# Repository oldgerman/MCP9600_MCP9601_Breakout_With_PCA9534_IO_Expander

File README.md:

# MCP9600/MCP9601 Breakout, With PCA9534 IO Expander 

- <span style="color:rgb(255, 0, 0);">The module has a bug, don’t make a board.</span>
- <span style="color:rgb(255, 0, 0);">该模块有BUG，不要打板</span>

## PCB

## SCH

## BOM

Please see bom/ibom.html

## Connectors

1. 5.08mm Pitch 2Pin Plug

2. [OMEGA Circuit Board Thermocouple Connectors](https://www.omega.com/en-us/temperature-measurement/temperature-connectors%2C-panels-and-block-assemblies/temperature-connectors/p/PCC-OST-SMP)

## Pictures

:confused:

## Libraries

1. [PCA9534](https://github.com/alotaiba/PCA9534)
2. [MCP9600](https://github.com/sparkfun/SparkFun_MCP9600_Arduino_Library)

## Reference

1. [Microchip：MCP9600 Evaluation Board](https://www.microchip.com/adm00665-063015a)

2. [Maxim：MAX31855PMB1 Peripheral Module](https://www.maximintegrated.com/en/products/sensors/MAX31855PMB1.html)

3. [Seeed：Grove - I2C Thermocouple Amplifier MCP9600](https://wiki.seeedstudio.com/Grove-I2C_Thermocouple_Amplifier-MCP9600/)

4. [SparkFun：Qwiic Thermocouple Amplifier - MCP9600](https://www.sparkfun.com/products/16294)

5. [Adafruit：MCP9600 I2C Thermocouple Amplifier](https://www.adafruit.com/product/4101)

## Test

MCP96RL01 + T12 irons TYPE-N

| Read Thermocouple(℃) | Read Ambient(℃) | Measurements(mV) | (Ref Junction 0℃) its 90 table for N Type(mV) | (Ref Junction 0℃) its 90 table for N Type(℃) | Read Ambient + its 90 table N Type  (℃) | error(℃) | Hot air gun(W) |
| -------------------- | --------------- | ---------------- | --------------------------------------------- | -------------------------------------------- | --------------------------------------- | -------- | -------------- |
| 100                  | 24.62           | 2.1              | 2.106                                         | 78                                           | 102.62                                  | 2.62     | 314            |
| 156                  | 24.75           | 3.8              | 3.803                                         | 135                                          | 159.75                                  | 3.75     | 500            |
| 180                  | 24.56           | 4.6              | 4.618                                         | 160                                          | 184.56                                  | 4.56     | 587            |
| 190                  | 25.37           | 4.8              | 4.809                                         | 167                                          | 192.37                                  | 2.37     | 600            |

## Alert 引脚的下拉电阻

MCP9601的6个Alert引脚均为推挽输出，复位后默认状态为Alert1~4输出高电平，OC Alert和SC Alert均使能，高电平表示OC触发，SC触发，或温度警报触发，无PCF9534时，6个Alert引脚不需要下拉电阻，Alert的3.3V高电平可正常输出给MCU

若焊接了PCF9534，则PCF9534复位的寄存器默认值将io 0~7配置为高阻抗输出驱动器的输入，输入电压可以升高到VDD以上，最大为5.5V，此时需要焊接所有Alert pins的下拉电阻，确保Alert的高电平为3.3V

## Important premise of the data sheet

### 3.4 Push-Pull Alert Outputs (Alert 1, 2, 3, 4 and OC/SC Alert)

Alert引脚是用户可编程的推挽输出，可用于检测温度上升或下降。当环境温度超过用户设置的温度警报极限时，设备输出**高电平**信号。 对于MCP9601 / L01 / RL01，当在VSENSE引脚上检测到开路和短路条件时，OC Alert和SC Alert输出才有效，这两个Alerts也是**高电平有效**推挽输出

### 6.3.3.1开路检测技术

mcp9600和mcp9601都具有开路检测技术（即使mcp9600没有V<sub>SENSE</sub>和OC Alert引脚），区别在于mcp9601的OC Alert引脚可以当作硬件指示器

对于MCP9600 / L00 / RL00开路检测，可以使用STATUS寄存器（寄存器5-6）的输入范围位（位4）来检测开路条件。这将需要一些外部电阻，如图6-6所示。无源电路不会影响MCP9600 / L00 / RL00的精度（RB的推荐值设置为1M。连接热电偶时，输入共模电压为 0.5×VDD。当热电偶断开连接，VIN +输入端的电压为 0.66×VDD，VIN-输入端的电压下拉至VSS。此更改将强制设置输入范围位。

MCP9601 / L01 / RL01开路检测机制的工作原理类似（请参见图6-7），检测阈值指定为V<sub>SiOC</sub>和V<sub>SiNOR</sub>（请参见DC特性）。主控制器可以立即轮询状态位以检测开路条件。对于MCP9601 / L01 / RL01，可以将OC Alert引脚用作硬件指示器。

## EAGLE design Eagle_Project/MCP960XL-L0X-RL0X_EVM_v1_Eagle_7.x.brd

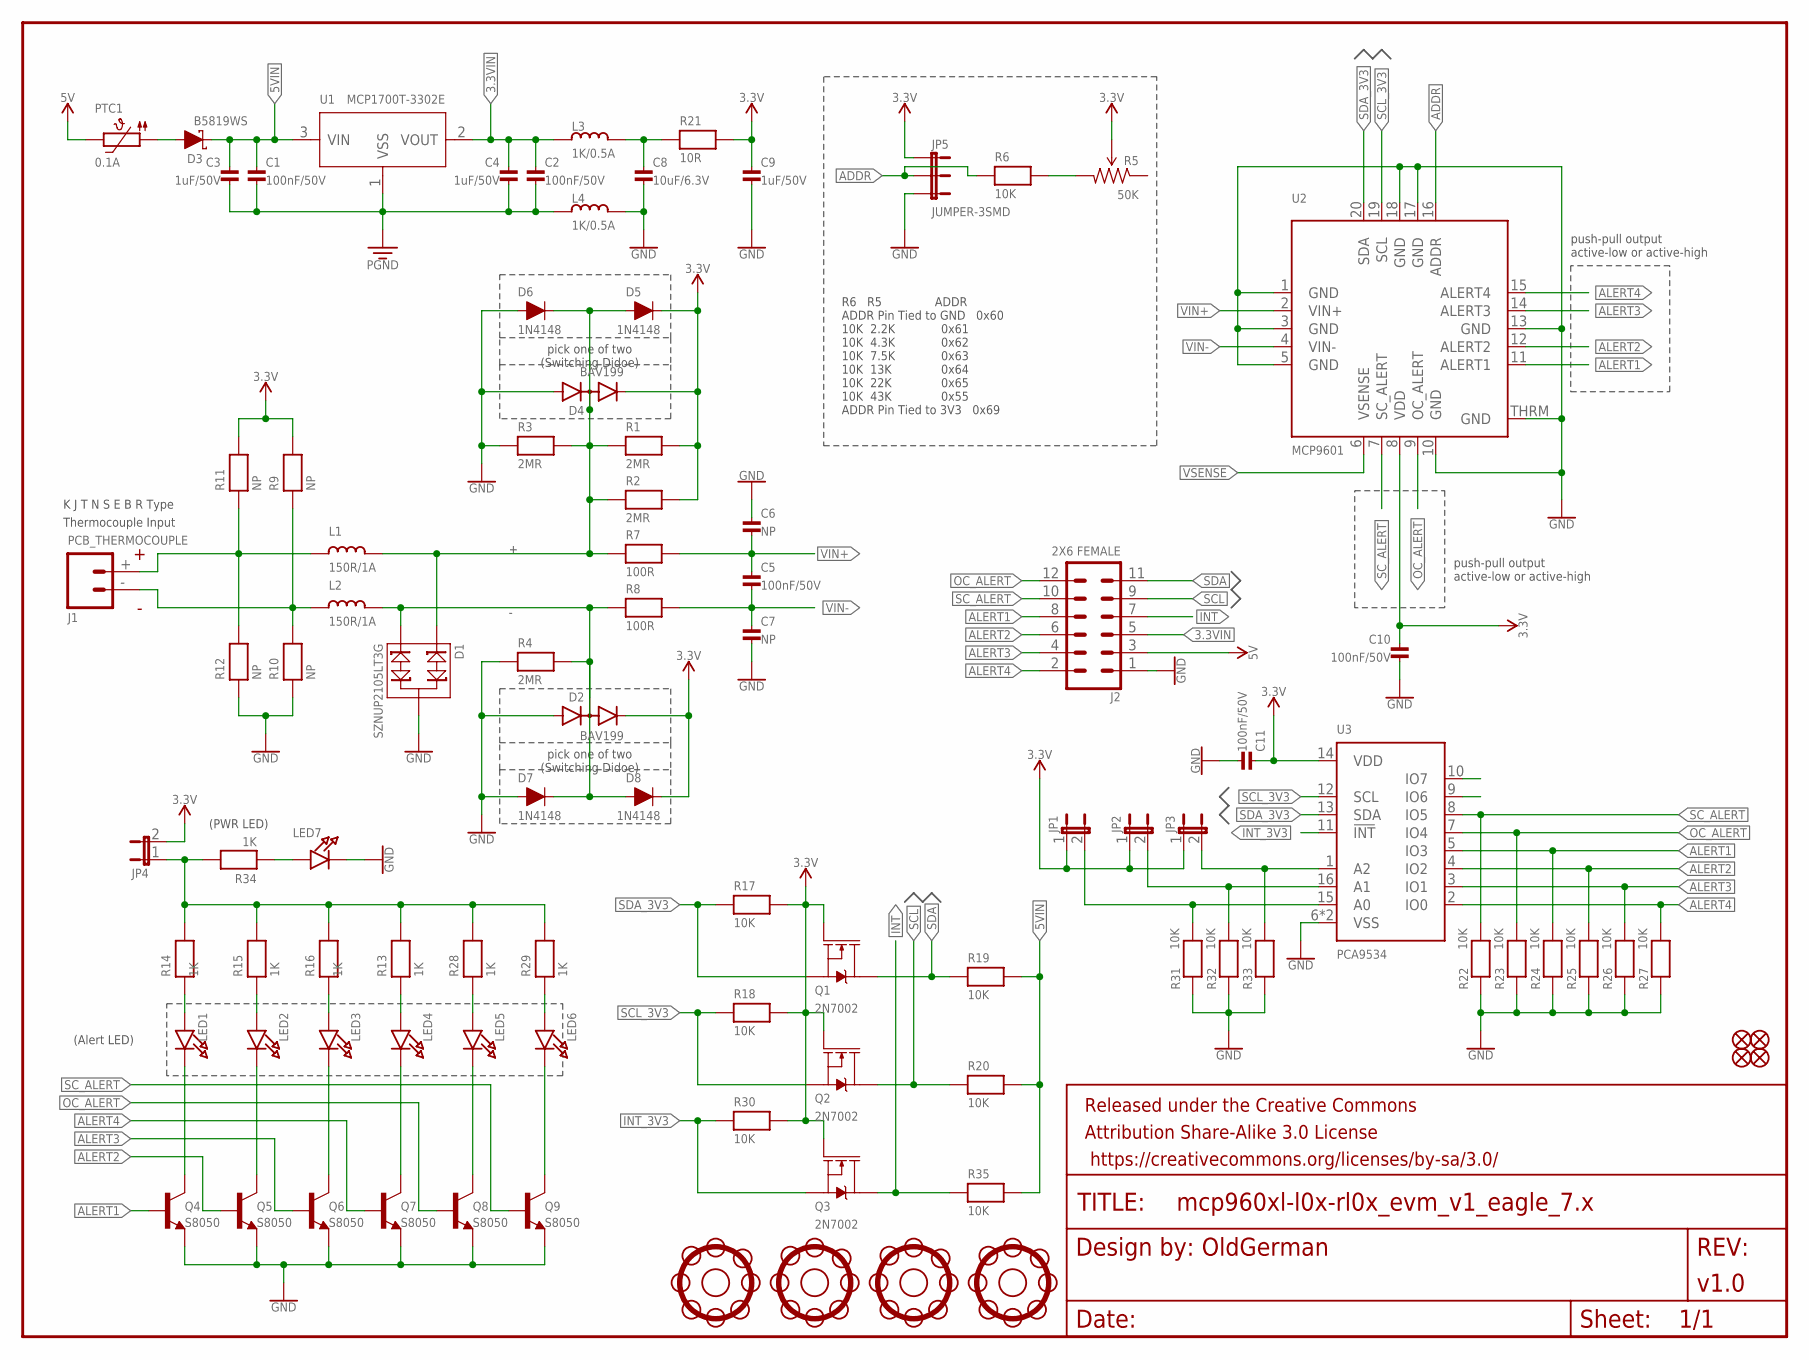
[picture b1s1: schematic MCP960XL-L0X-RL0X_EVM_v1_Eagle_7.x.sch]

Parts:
C1, C2, C5, C10, C11: 100nF/50V; 0603
C3, C4, C9: 1uF/50V; 0603
C6, C7: NP; 0603
C8: 10uF/6.3V; 0603
D1: SZNUP2105LT3G; SOT23-3
D2, D4: BAV199; SOT23-3
D3: B5819WS; SOD-323
D5, D6, D7, D8: 1N4148; SOD-323
FID1, FID2, FID3, FID4: FIDUCIAL1X2.5; FIDUCIAL-1X2.5
FRAME1: FRAME-LETTER; CREATIVE_COMMONS
J1: PCB_THERMOCOUPLE; PCC-SMP
J2: 2X6 FEMALE; 2X6
JP1, JP2, JP3, JP4: JUMPER-2SMD-NC; SJ_2S
JP5: JUMPER-3SMD; SJ_3
L1, L2: 150R/1A; 0603
L3, L4: 1K/0.5A; 0603
LED1, LED2, LED3, LED4, LED5, LED6, LED7: LED0603; CHIPLED_0603
PTC1: 0.1A; 1206
Q1, Q2, Q3: 2N7002; SOT23-3
Q4, Q5, Q6, Q7, Q8, Q9: S8050; SOT23-3
R1, R2, R3, R4: 2MR; 0603
R5: 50K; TRIMPOT-3MM
R6, R17, R18, R19, R20, R22, R23, R24, R25, R26, R27, R30, R31, R32, R33, R35: 10K; 0603
R7, R8: 100R; 0603
R9, R10, R11, R12: NP; 0603
R13, R14, R15, R16, R28, R29, R34: 1K; 0603
R21: 10R; 0603
U1: MCP1700T-3302E; SOT23-3
U2: MCP9601; VQFN20_5MM
U3: PCA9534; HVQFN16_4X4_0.65MM
U$1, U$3, U$4, U$6: SUN_HOLE_M3

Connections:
3.3V: C9.1, C10.1, C11.1, D2.3 (C), D4.3 (C), D5.C, D8.C, JP1.1, JP2.1, JP3.1, JP4.2, JP5.1, Q1.1 (G), Q2.1 (G), Q3.1 (G), R1.2, R2.2, R5.2 (WIPER), R9.2, R11.2, R17.2, R18.2, R21.2, R30.2, U2.8 (VDD), U3.14 (VDD)
3.3VIN: C2.1, C4.1, J2.5, L3.1, U1.2 (VOUT)
5V: J2.3, PTC1.2
5VIN: C1.1, C3.1, D3.C, R19.2, R20.2, R35.2, U1.3 (VIN)
A0: JP1.2, R31.2, U3.15 (A0)
A1: JP2.2, R32.2, U3.16 (A1)
A2: JP3.2, R33.2, U3.1 (A2)
ADDR: JP5.2, R6.1, U2.16 (ADDR)
ALERT1: J2.8, Q4.1 (B), R24.2, U2.11 (ALERT1), U3.5 (IO3)
ALERT2: J2.6, Q5.1 (B), R25.2, U2.12 (ALERT2), U3.4 (IO2)
ALERT3: J2.4, Q6.1 (B), R26.2, U2.14 (ALERT3), U3.3 (IO1)
ALERT4: J2.2, Q7.1 (B), R27.2, U2.15 (ALERT4), U3.2 (IO0)
GND: C6.1, C7.2, C8.2, C9.2, C10.2, C11.2, D1.3, D2.1 (A), D4.1 (A), D6.A, D7.A, J2.1, JP5.3, L4.2, LED7.C, Q4.2 (E), Q5.2 (E), Q6.2 (E), Q7.2 (E), Q8.2 (E), Q9.2 (E), R3.1, R4.1, R10.1, R12.1, R22.1, R23.1, R24.1, R25.1, R26.1, R27.1, R31.1, R32.1, R33.1, U2.1 (GND), U2.3 (GND), U2.5 (GND), U2.10 (GND), U2.13 (GND), U2.17 (GND), U2.18 (GND), U2.THRM (GND), U3.6 (VSS), U3.PAD (VSS)
INT: J2.7, Q3.3 (D), R35.1
INT_3V3: Q3.2 (S), R30.1, U3.11 (!INT)
L1_OUT: D1.1, D4.2 (AC), D5.A, D6.C, L1.2, R1.1, R2.1, R3.2, R7.1
L2_OUT: D1.2, D2.2 (AC), D7.C, D8.A, L2.2, R4.2, R8.1
unnamed: R5.1 (CW), R6.2
unnamed: C8.1, L3.2, R21.1
unnamed: LED4.C, Q7.3 (C)
unnamed: LED4.A, R13.1
unnamed: LED7.A, R34.1
unnamed: LED5.C, Q8.3 (C)
unnamed: LED1.C, Q4.3 (C)
unnamed: LED5.A, R28.1
unnamed: LED6.C, Q9.3 (C)
unnamed: LED1.A, R14.1
unnamed: LED2.C, Q5.3 (C)
unnamed: LED2.A, R15.1
unnamed: LED3.C, Q6.3 (C)
unnamed: LED3.A, R16.1
unnamed: LED6.A, R29.1
unnamed: D3.A, PTC1.1
unnamed: JP4.1, R13.2, R14.2, R15.2, R16.2, R28.2, R29.2, R34.2
OC_ALERT: J2.12, Q8.1 (B), R23.2, U2.9 (OC_ALERT), U3.7 (IO4)
PGND: C1.2, C2.2, C3.2, C4.2, L4.1, U1.1 (VSS)
SCL: J2.9, Q2.3 (D), R20.1
SCL_3V3: Q2.2 (S), R18.1, U2.19 (SCL), U3.12 (SCL)
SC_ALERT: J2.10, Q9.1 (B), R22.2, U2.7 (SC_ALERT), U3.8 (IO5)
SDA: J2.11, Q1.3 (D), R19.1
SDA_3V3: Q1.2 (S), R17.1, U2.20 (SDA), U3.13 (SDA)
TH+: J1.+, L1.1, R11.1, R12.2
TH-: J1.-, L2.1, R9.1, R10.2
VIN+: C5.1, C6.2, R7.2, U2.2 (VIN+)
VIN-: C5.2, C7.1, R8.2, U2.4 (VIN-)
VSENSE: U2.6 (VSENSE)

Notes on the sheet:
Thermocouple Input
K J T N S E B R Type
push-pull output active-low or active-high
pick one of two (Switching Didoe)
(PWR LED)
(Alert LED)
R6 R5 ADDR ADDR Pin Tied to GND 0x60 10K 2.2K 0x61 10K 4.3K 0x62 10K 7.5K 0x63 10K 13K 0x64 10K 22K 0x65 10K 43K 0x55 ADDR Pin Tied to 3V3 0x69
OldGerman
v1.0

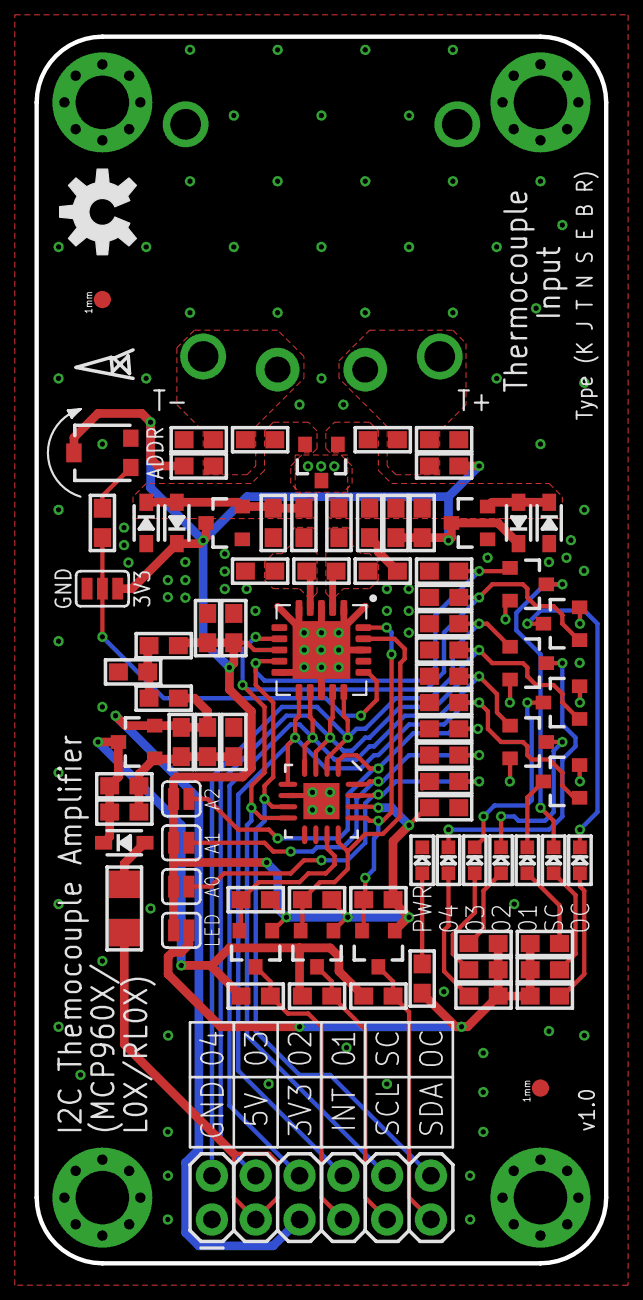
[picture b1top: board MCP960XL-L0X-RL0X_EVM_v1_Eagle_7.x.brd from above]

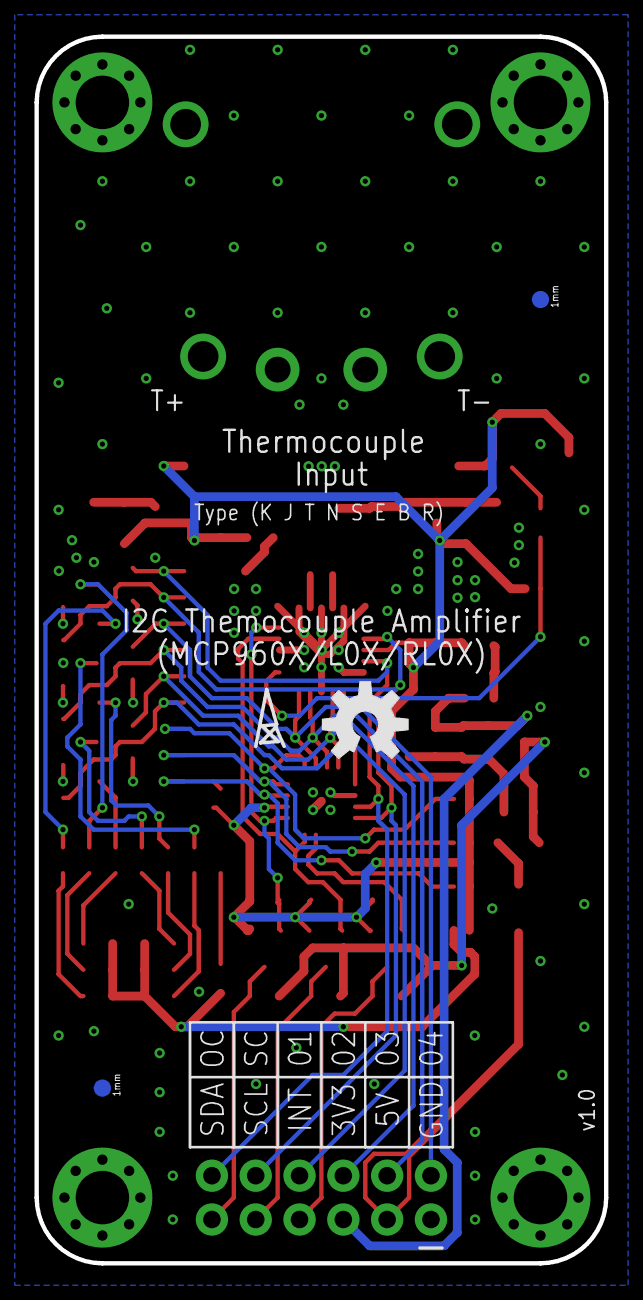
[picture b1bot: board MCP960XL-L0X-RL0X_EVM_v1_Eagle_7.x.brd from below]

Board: 2 copper layers, 33.0 x 71.1 mm, 96 parts (4 on the bottom side), 45 nets.

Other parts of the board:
U$2, U$5: OSHW-LOGO-M

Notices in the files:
parts and their libraries:
microbuilder: This work is placed in the public domain, and may be freely used for commercial and non-commercial work with the following conditions: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
SparkFun-DiscreteSemi: Licensing: Creative Commons ShareAlike 4.0 International - https://creativecommons.org/licenses/by-sa/4.0
